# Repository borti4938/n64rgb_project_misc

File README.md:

Miscellaneous PCBs for the N64RGB Project
---

This repository contains several PCBs which I find to be helpful for the N64RGB project.
Here is a small overview.

- [Filter AddOn](./FilterAddOn/): A tiny PCB which adds a video filter to the MultiOut for the analog output
- [Flex PCB N64RGB to MultiOut](./N64RGB2MoutFilter/): A flexible PCB which connects between N64RGBv2.1 or N64Advanced and MultiOut. This flexible is designed to have the filter add on included if wanted.
- [Power Regulator](./PowerReg/): A power regulator connecting to 12V power rail and outputting 3.3V for older N64RGB PCBs (earlier than v2.1) and viletims commercial N64RGB product.
- [Flex PCB RCP-NUS to N64RGB](./RCP2N64RGB/): A flexible PCB which connects between RCP-NUS and N64RGBv2.1 or N64Advanced.
- [Flex PCB RCP-NUS to some wire pads](./RCP2Pads/): A tiny flexible PCB which connects to the RCP-NUS optimized for price. This helps installing a CPLD-/FPGA-based N64RGB PCB with wires to the digital video lines.
- [A simple N64RGB Amp](./simpleRGBamp/): A THS7374 board mostly suitable for a N64 which already outputs RGB (-CPU-01 to -CPU-04 boards).

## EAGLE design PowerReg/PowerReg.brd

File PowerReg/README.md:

Power Regulator for N64RGB DAC
---

### Purpose

This little PCB is designed to used with
- [viletims N64RGB](http://etim.net.au/n64rgb/) project
- older boards from the [N64RGBv1 project](https://github.com/borti4938/n64rgb/tree/master/generalRGBmod/Main-PCB/v1)

This PCB has a regulator on board which generated 3.3V power supply for the mentioned mod-boards. It has been discussed at the [Shmups forums](https://shmups.system11.org/viewtopic.php?f=6&t=61455) that the output suffers from digital noise probably depending on CPU, PPU and APU load.  
Power the replacement RGB DAC from a different power supply source may help to 'decouple' this noise from the analog part.

##### Note
**[1]** Future releases may have a regulator on board. It has not been designed yet.

### Buiding the PCB

You may use any PCB prototype service of your choice or use a pre-existing [OSHPark project](https://oshpark.com/shared_projects/ofIFYk5I).  
**Order the board as thin as possible**; <1.0mm should be fine. This means for OSHPark service use 0.8mm substrate thickness.

### BOM

- U1: one of the following ICs, all SOT223 package (may named differently for each manufacturer)
  - NCP1117ST33T3G
  - TLV1117-33IDCYR
  - SPX1117M3-L-3-3/TR
- C1: 10-100uF/16V+ (SMD0805-1210)
- C2: 10-100uF/6.3V+ (SMD0805-1210)
- C3: 2.2uF / 6.3V+ (SMD0603)

### Installation

0. If not already done: assemble the PCB.
1. If you have an existing installation, first disconnect the 3.3V power supply wire from the modding board.  
   (Please look onto the pin out diagrams if you use viletims board - it may be one wire of the ribbon cable)
2. Solder the PCB under the power switch of the N64 mainboard (upper part) such that the PCB ranges to the inner side.
3. Connect the 3.3V output to the modding PCB

## ENJOY!!!!

### Acknowledgement

Many thanks to Womi ([circuit-board.de](https://circuit-board.de/forum/) user) for testing and giving feedback.  
Also many thanks to the shmups community for the discussion, especially but not limited to leonk, Syntax, kel, viletim, Thomas83lin, and many more...

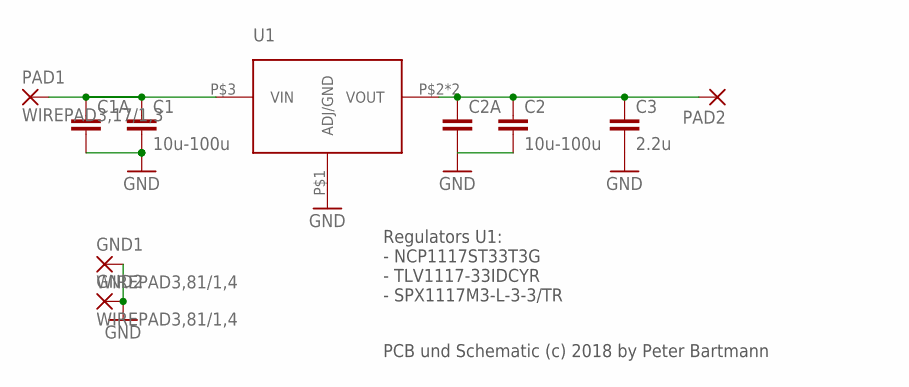
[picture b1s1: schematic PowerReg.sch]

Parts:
C1, C2: 10u-100u; C0805
C1A, C2A: C-EUC1210K; C1210K
C3: 2.2u; C0603
GND1, GND2: WIREPAD3,81/1,4; 3,81/1,4
PAD1: WIREPAD3,17/1,3; 3,17/1,3
PAD2: SMD5; SMD2,54-5,08
U1: SPX1117; SOT-223

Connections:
GND: C1.2, C1A.2, C2.2, C2A.2, C3.2, GND1.1, GND2.1, U1.P$1 (ADJ/GND)
unnamed: C1.1, C1A.1, PAD1.1, U1.P$3 (VIN)
unnamed: C2.1, C2A.1, C3.1, PAD2.1, U1.P$2 (VOUT), U1.P$4 (VOUT)

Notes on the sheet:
Regulators U1: - NCP1117ST33T3G - TLV1117-33IDCYR - SPX1117M3-L-3-3/TR
PCB und Schematic (c) 2018 by Peter Bartmann

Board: 2 copper layers, 10 parts (0 on the bottom side), 3 nets, no tracks yet.

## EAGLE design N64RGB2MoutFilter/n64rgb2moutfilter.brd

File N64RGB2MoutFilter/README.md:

N64RGB2MoutFilter
---

A **flexible** PCB which connects the MultiOut with the [N64 Advanced PCB](https://github.com/borti4938/n64adv_pcb) or [N64RGB PCB](https://github.com/borti4938/n64rgb_pcb).
The connection PCB must be soldered on both ends - one end goes to the MultiOut, the other to the modding board.
To support older PCBs, I decided to go with the solder solution.
I future updates I may replace that and go with a FFC connector on the modding board side.

### Ordering the PCB

You can order the PCB from any manufacturer you like.
OSHPark flex service is fine, also the flex service from PCBWay does a great job.

### Assembly

Order the PCB and source the components as requested by the [BOM sheet](./doc/N64RGB2MoutFilter_BOM.xlsx).
Assembly should be straight forward.
You may print the [assembly sheet](./doc/n64rgb2multiout_assembly_sheet_top.pdf) for your orientation.

Please note that you have the option to include the [Filter AddOn](../FilterAddOn) on the flexible PCB or just leave it.
I recommend using the filter.

If you use a PCBA service, you may use the provided mounting file ([with filter](./doc/n64rgb2moutfilter_filteroption.mnt) or [without filter](./doc/n64rgb2moutfilter_nofilter.mnt)).

### Installation

Please read the installation guide of the [N64 Advanced PCB](https://github.com/borti4938/n64adv_pcb) or [N64RGB PCB](https://github.com/borti4938/n64rgb_pcb).

### Jumper Description

Use of SJ1 and SJ3 is also described in the installation guide of the [N64 Advanced PCB](https://github.com/borti4938/n64adv_pcb) or [N64RGB PCB](https://github.com/borti4938/n64rgb_pcb).
Just follow this guide and you came across to the point where you work with them.

#### SJ1

Jumper matrix determine sync source at MultiOut
 - Jumper at 1a forwarding TTL sync
 - Jumper at 1b forwarding 75ohm sync
 - number next to each particular jumper determines the pin of the MultiOut where the signal is forwarded to
 - You are not allowed to short two times the same number!
 
Examples:
 - Closing _1a - 3_ forwards TTL sync to pin 3 of the MultiOut
 - Closing _1b - 7_ forwards 75ohm sync to pin 7 of the MultiOut
 - It is not allowed to close _1a - 3_ and _1b - 3_ at the same time
 - It is allowed to close _1b - 3_, _1b - 7_ and _1b - 9_ at the same time

#### SJ2

flex assembly setup (see [BOM sheet](./doc/N64RGB2MoutFilter_BOM.xlsx))
 - close all three jumpers if you do not use the filter assembly

#### SJ3

Sync source at the modding board
 - J3.1: Use TTL C-Sync (true TTL setup)
 - J3.2: Use 75ohm Sync (75ohm setup)
 - Never use both!

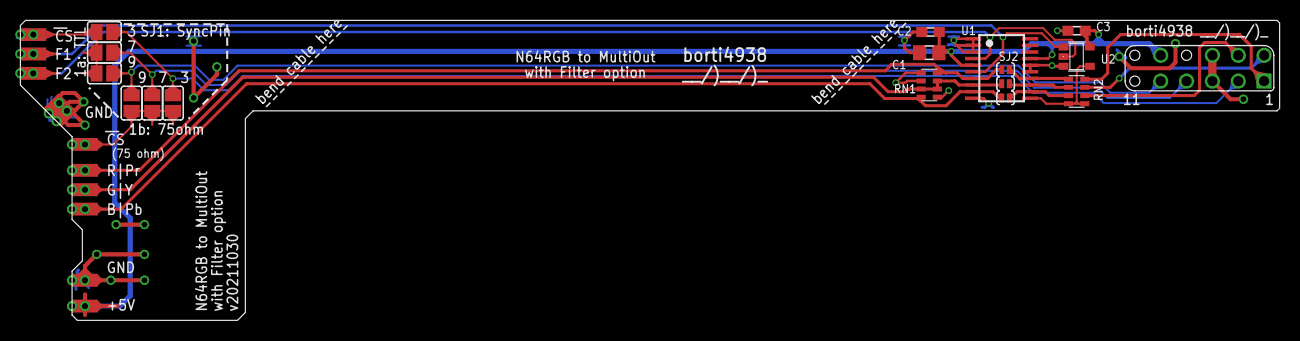
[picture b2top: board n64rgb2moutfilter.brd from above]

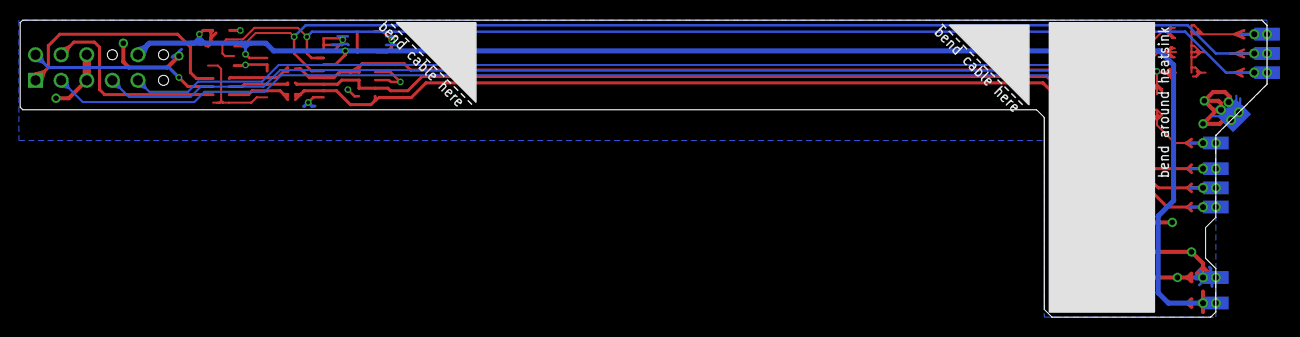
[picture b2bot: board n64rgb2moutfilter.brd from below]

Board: 2 copper layers, 123.7 x 29.5 mm, 39 parts (11 on the bottom side), 19 nets.

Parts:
B/PB, B/PB1: SMD1,27-2,54
C1: 22u; C0805
C2, C3: 0.1u; C0603
CS75#, CS75#1: SMD1,27-2,54
CS#, CS#1: SMD1,27-2,54
E$1: SNES_MULTIAV_RGBSYFBAS
E$2, E$3, E$4, E$5, E$6, E$7: SJ
F1, F2, F3, F4: SMD1,27-2,54
G/Y, G/Y1: SMD1,27-2,54
P_GND1, P_GND2, P_GND3, P_GND4, P_GND5, P_GND6: SMD1,27-2,54
P_VCC_5V, P_VCC_5V1: SMD1,27-2,54
R/PR, R/PR1: SMD1,27-2,54
RN1, RN2: 75; CTS742C083
SJ2B, SJ2G, SJ2R: SJ_SMALL
U1: THS7368
U2: SOT23-5

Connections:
5V: C1.2, C2.1, C3.1, E$1.10, P_VCC_5V.1, P_VCC_5V1.1, U1.5, U1.17, U2.5
#CS: E$1.3, E$2.2, E$7.2
#CS.75.I: CS75#.1, CS75#1.1, E$5.1, E$6.1, E$7.1
#CS.I: CS#.1, CS#1.1, E$2.1, E$3.1, E$4.1
BLUE: B/PB.1, B/PB1.1, RN1.8, SJ2R.1, U1.9
BLUE.OUT: RN2.3, SJ2R.2, U1.12
BLUE.OUT.75: E$1.4, RN2.6
BYPASS_SF: RN2.4, RN2.5, U1.11, U2.4
F1: F1.1, F4.1, U1.6, U2.1
F2: F2.1, F3.1, U1.4, U2.2
FBAS: E$1.9, E$4.2, E$5.2
GND: C1.1, C2.2, C3.2, E$1.5, E$1.6, P_GND1.1, P_GND2.1, P_GND3.1, P_GND4.1, P_GND5.1, P_GND6.1, RN1.1, RN1.5, RN1.6, U1.1, U1.2, U1.3, U1.10, U1.15, U1.16, U2.3
GREEN: G/Y.1, G/Y1.1, RN1.2, RN1.3, RN1.7, SJ2G.1, U1.8
GREEN.OUT: RN2.2, SJ2G.2, U1.13
GREEN.OUT.75: E$1.2, RN2.7
LUMA: E$1.7, E$3.2, E$6.2
RED: R/PR.1, R/PR1.1, RN1.4, SJ2B.1, U1.7
RED1.OUT: RN2.1, SJ2B.2, U1.14
RED.OUT.75: E$1.1, RN2.8

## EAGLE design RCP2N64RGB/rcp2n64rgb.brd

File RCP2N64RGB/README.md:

RCP2N64RGB
---

A **flexible** PCB which connects the RCP-NUS (graphical processor of the N64) with the [N64 Advanced PCB](https://github.com/borti4938/n64adv_pcb) or [N64RGB PCB](https://github.com/borti4938/n64rgb_pcb).
The connection PCB must be soldered on both ends - one end goes to the RCP-NUS, the other to the modding board.
To support older PCBs, I decided to go with the solder solution.
I future updates I may replace that and go with a FFC connector on the modding board side.

### Ordering the PCB

You can order the PCB from any manufacturer you like.
OSHPark flex service is fine, also the flex service from PCBWay does a great job.

### Assembly

Order the PCB and source the components as requested by the [BOM sheet](./doc/RCP2N64RGB_BOM.xlsx).
Assembly should be straight forward.
The ferrite bead / resistor arrays don't have an orientation.

You may print the [assembly sheet](./doc/rcp2n64rgb_assembly_sheet_top.pdf) for your orientation.
If you use a PCBA service, you may use the provided [mounting file](./doc/rcp2n64rgb.mnt).

### Installation

Please read the installation guide of the [N64 Advanced PCB](https://github.com/borti4938/n64adv_pcb) or [N64RGB PCB](https://github.com/borti4938/n64rgb_pcb).

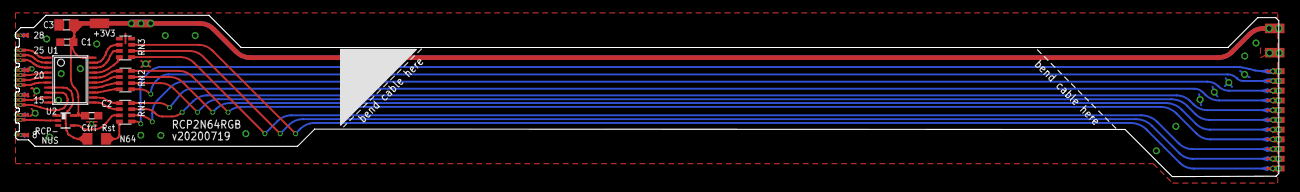
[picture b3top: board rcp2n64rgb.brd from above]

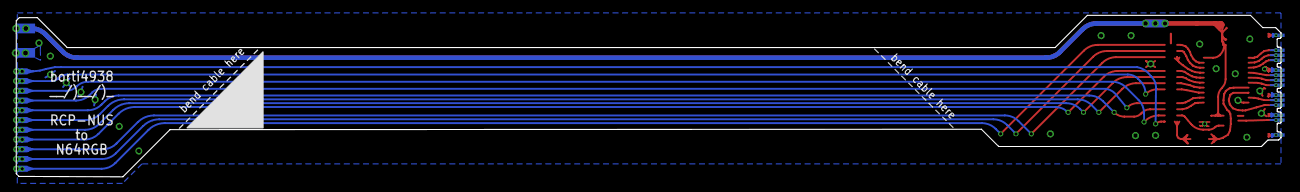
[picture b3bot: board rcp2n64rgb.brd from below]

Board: 2 copper layers, 164.9 x 21.1 mm, 65 parts (27 on the bottom side), 34 nets.

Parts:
/RST_A, /RST_A1: SMD0,8-1,6
C1, C2: 0.1u; C0603
C3: 22u; C0805
CLOCK#, CLOCK#1: SMD0,8-1,6
CTRL_A, CTRL_A1: SMD0,8-1,6
D0, D1, D2, D3, D4, D5, D6, D7, D8, D9, D10, D11, D12, D13: SMD0,8-1,6
DSYNC#, DSYNC#1: SMD0,8-1,6
E$2, E$6: SMD0.8SQ
E$8, E$9, E$10, E$11, E$12, E$13, E$14, E$15, E$16, E$17, E$18, E$19, E$22, E$23, E$24, E$25, E$26, E$27, E$28, E$29, E$30, E$31, E$32, E$33, E$43, E$46, E$47: SMD0,45-1,35
GND: SMD0,45-1,35
P_GND0, P_GND1: SMD1,27-2,54
P_VCC_3V, P_VCC_3V1, P_VCC_3V3: SMD1,27-2,54
RN1, RN2, RN3: CTS742C083
U1: 74VHC9151FT; TSSOP20
U2: SN74LVC1G17DCKR; DCK_R-PDSO-G5

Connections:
3V3: C1.1, C2.1, C3.1, P_VCC_3V.1, P_VCC_3V1.1, P_VCC_3V3.1, U1.20, U2.5
#DSYNC: E$10.P$1, E$31.P$1, U1.8
#DSYNC.1: DSYNC#.P$1, DSYNC#1.P$1, RN1.8
CTRL: E$2.P$1, U1.7
CTRL.1: CTRL_A.P$1, CTRL_A1.P$1, RN2.5
D0: E$19.P$1, E$22.P$1, U1.1
D0.1: D0.P$1, D7.P$1, RN3.7
D1: E$18.P$1, E$23.P$1, U1.2
D1.1: D1.P$1, D8.P$1, RN3.6
D2: E$17.P$1, E$24.P$1, U1.3
D2.1: D2.P$1, D9.P$1, RN3.5
D3: E$15.P$1, E$26.P$1, U1.4
D3.1: D3.P$1, D10.P$1, RN2.8
D4: E$14.P$1, E$27.P$1, U1.5
D4.1: D4.P$1, D11.P$1, RN2.7
D5: E$13.P$1, E$28.P$1, U1.6
D5.1: D5.P$1, D12.P$1, RN2.6
D6: E$11.P$1, E$30.P$1, U1.9
D6.1: D6.P$1, D13.P$1, RN1.7
GND: C1.2, C2.2, C3.2, E$9.P$1, E$12.P$1, E$16.P$1, E$25.P$1, E$29.P$1, E$32.P$1, E$43.P$1, E$46.P$1, GND.P$1, P_GND0.1, P_GND1.1, RN3.1, RN3.8, U1.10, U2.3
RST: E$6.P$1, RN1.4
RST.1: /RST_A.P$1, /RST_A1.P$1, RN1.5
S$1: RN3.2, U1.19
S$2: RN3.3, U1.18
S$3: RN3.4, U1.17
S$4: RN2.1, U1.16
S$6: RN2.2, U1.15
S$7: RN2.3, U1.14
S$9: RN1.1, U1.12
S$10: RN2.4, U1.13
S$11: RN1.3, U2.4
S$12: RN1.2, U1.11
VCLK: E$8.P$1, E$33.P$1, U2.2
VCLK.1: CLOCK#.P$1, CLOCK#1.P$1, RN1.6

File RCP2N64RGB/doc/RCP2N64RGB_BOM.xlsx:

No. of PCBs | 3
Designator | MPN | QTY per PCB | QTY | DESCRIPTION | VALUE | PACKAGE | NOTES
U1 | 74VHC9151FT | 1 | 3 | 9bit Buffer, Schmitt-Triggered, non-inverting |  | TSSOP20
U2 | SN74LVC1G17DCKR | 1 | 3 | Buffer, Schmitt-Triggered, non-inverting |  | SO70-5
C1,C2 |  | 1 | 3 | Ceramic capacitor, X8L | 0.1uF / 50V | SMD0603
C3 |  | 1 | 3 | Ceramic capacitor, X5R | 22uF / 6.3V | SMD0805
RN1,RN2,RN3 | BK32164M121-T | 3 | 9 | Resistor Array (4x) | 4x ferrit bead | SMD1206 | Either this, …
 | CAT16-000J4LF / CAY16-000J4LF |  |  | Resistor Array (4x) | 4x 0ohm | SMD1206 | … or that for RN1-RN3

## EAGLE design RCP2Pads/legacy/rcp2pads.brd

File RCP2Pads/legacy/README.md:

# A small Flex-PCB
## N64 RCP-NUS breakout

## Purpose

This PCB enables you to apply conditioning resistors to the RCP output pins. This is useful for any CPLD and FPGA RGB Kit like viletims N64RGB (public and commercial), N64RGBv1, N64RGBv2, N64Advanced and many more variations spread over the internet.

## Pinout

From top to bottom (RCP on left, connector right)

| **Pin** | **Signal** |
|:-------:|:-----------|
| 17 | GND |
| 16 | D0 |
| 15 | D1 |
| 14 | D2 |
| 13 | D3 |
| 12 | D4 |
| 11 | D5 |
| 10 | D6 |
| 9 | #DSYNC |
| 8 | VCLK |
| 7 | GND |
| 6 | LRCLK (Audio, A2) |
| 5 | SDATA (Audio, A1) |
| 4 | SCLK (Audio, A0) |
| 3 | GND |
| 2 | Ctrl. (controller port pin 2, pin 16 PIF-NUS) |
| 1 | Rst (pin 27 PIF-NUS) |

## Preparation

You need

- four resistor arrays: 4x47ohm parallel, SMD1206, e.g. CAT16-47R0F4LF / CAY16-47R0F4LF
- if you have resistors at the input of your N64RGB modding board, you need to replace them with ferrite beads (see BOM if for proper replacements)

Assemble the board. The resistor arrays don't have an orientation.

## Installation

Solder the FPC board to the output pins 6 - 28 (pin 5 has a dot, pin 30 also) of the RCP-NUS.

Connect pad for Ctrl. and Rst. as stated in the table above. More information about appropriate solder points can be found in the Guide.

Use the pads to connect your modding kit. Note the pinout of the modding kit. If possible, keep/run VCLK separated from data wires.

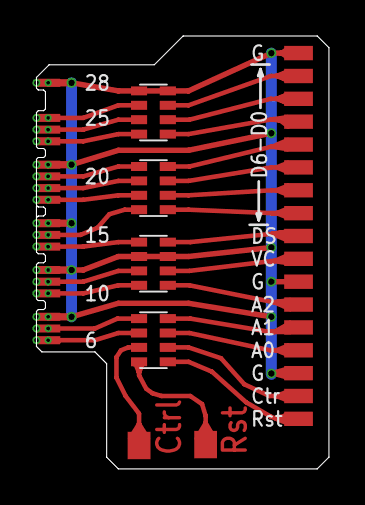
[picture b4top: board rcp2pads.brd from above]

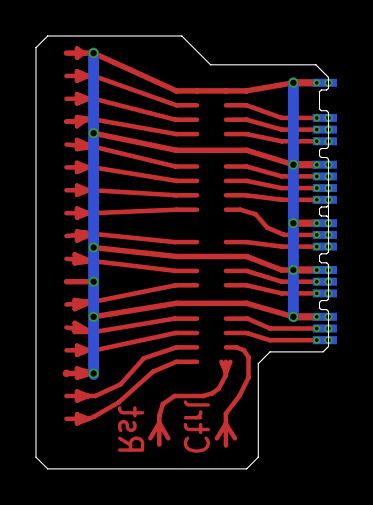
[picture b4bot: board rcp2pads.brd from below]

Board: 2 copper layers, 16.2 x 24.1 mm, 57 parts (17 on the bottom side), 29 nets.

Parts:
E$1, E$3, E$4, E$5: CTS742C083
E$2, E$6: SMD0.8SQ
E$8, E$9, E$10, E$11, E$12, E$13, E$14, E$15, E$16, E$17, E$18, E$19, E$22, E$23, E$24, E$25, E$26, E$27, E$28, E$29, E$30, E$31, E$32, E$33, E$38, E$40, E$41, E$42, E$43, E$44, E$45, E$46, E$47: SMD0,45-1,35
E$20, E$21, E$36, E$39, E$48, E$49, E$50, E$51, E$53, E$54, E$55, E$56, E$57, E$58, E$59, E$60, E$61: SMD0,8-1,6
GND: SMD0,45-1,35

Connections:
#DSYNC: E$5.1, E$10.P$1, E$31.P$1
#DSYNC.1: E$5.8, E$53.P$1
CTRL: E$1.7, E$2.P$1
CTRL.1: E$1.2, E$60.P$1
D0: E$3.2, E$19.P$1, E$22.P$1
D0.1: E$3.7, E$20.P$1
D1: E$3.3, E$18.P$1, E$23.P$1
D1.1: E$3.6, E$36.P$1
D2: E$3.4, E$17.P$1, E$24.P$1
D2.1: E$3.5, E$39.P$1
D3: E$4.1, E$15.P$1, E$26.P$1
D3.1: E$4.8, E$48.P$1
D4: E$4.2, E$14.P$1, E$27.P$1
D4.1: E$4.7, E$49.P$1
D5: E$4.3, E$13.P$1, E$28.P$1
D5.1: E$4.6, E$50.P$1
D6: E$4.4, E$11.P$1, E$30.P$1
D6.1: E$4.5, E$51.P$1
GND: E$3.1, E$3.8, E$5.2, E$5.7, E$9.P$1, E$12.P$1, E$16.P$1, E$21.P$1, E$25.P$1, E$29.P$1, E$32.P$1, E$43.P$1, E$46.P$1, E$55.P$1, E$59.P$1, GND.P$1
LRCLK: E$5.4, E$38.P$1
LRCLK.1: E$5.5, E$56.P$1
RST: E$1.8, E$6.P$1
RST.1: E$1.1, E$61.P$1
SCLK: E$1.6, E$41.P$1
SCLK.1: E$1.3, E$58.P$1
SDATA: E$1.5, E$40.P$1
SDATA.1: E$1.4, E$57.P$1
VCLK: E$5.3, E$8.P$1, E$33.P$1
VCLK.1: E$5.6, E$54.P$1

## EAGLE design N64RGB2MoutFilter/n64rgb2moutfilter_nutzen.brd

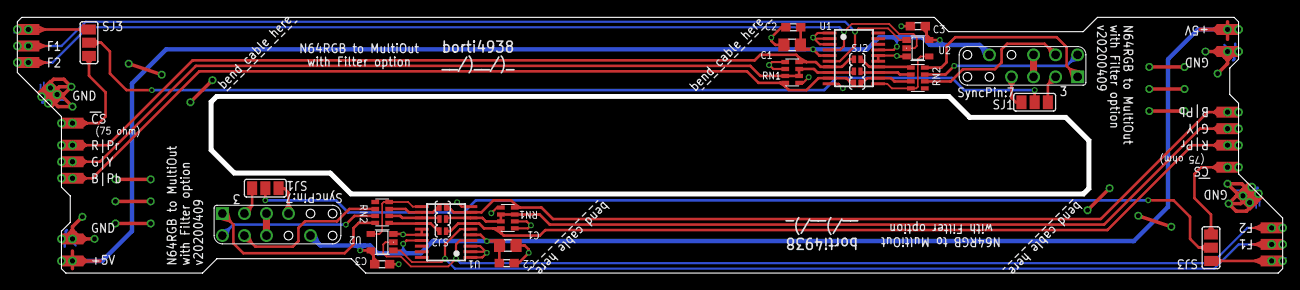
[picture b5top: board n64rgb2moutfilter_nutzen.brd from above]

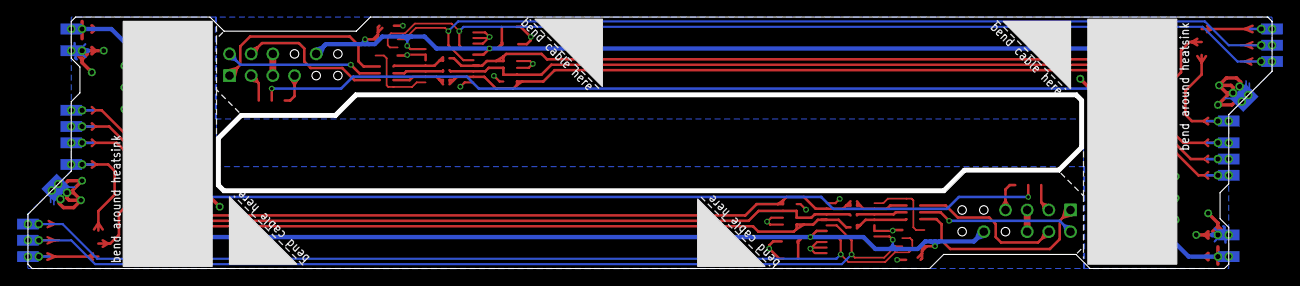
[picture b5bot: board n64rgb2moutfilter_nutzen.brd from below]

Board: 2 copper layers, 145.8 x 29.5 mm, 70 parts (22 on the bottom side), 38 nets.

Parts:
B/PB, B/PB1, B/PB2, B/PB3: SMD1,27-2,54
C1, C4: 22u; C0805
C2, C3, C5, C6: 0.1u; C0603
CS75#, CS75#1, CS75#2, CS75#3: SMD1,27-2,54
CS#, CS#1, CS#2, CS#3: SMD1,27-2,54
E$1, E$2: SNES_MULTIAV_RGBSY
F1, F2, F3, F4, F5, F6, F7, F8: SMD1,27-2,54
G/Y, G/Y1, G/Y2, G/Y3: SMD1,27-2,54
P_GND1, P_GND2, P_GND3, P_GND4, P_GND5, P_GND6, P_GND7, P_GND8, P_GND9, P_GND10, P_GND11, P_GND12: SMD1,27-2,54
P_VCC_5V, P_VCC_5V1, P_VCC_5V2, P_VCC_5V3: SMD1,27-2,54
R/PR, R/PR1, R/PR2, R/PR3: SMD1,27-2,54
RN1, RN2, RN3, RN4: 75; CTS742C083
SJ1, SJ2, SJ3, SJ4: SJ_2
SJ2B, SJ2B1, SJ2G, SJ2G1, SJ2R, SJ2R1: SJ_SMALL
U1, U3: THS7368
U2, U4: SOT23-5

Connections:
5V: C1.2, C2.1, C3.1, E$1.10, P_VCC_5V.1, P_VCC_5V1.1, U1.5, U1.17, U2.5
5V1: C4.2, C5.1, C6.1, E$2.10, P_VCC_5V2.1, P_VCC_5V3.1, U3.5, U3.17, U4.5
#CS: E$1.3, SJ1.1
#CS1: E$2.3, SJ2.1
#CS.75.I: CS75#.1, CS75#1.1, SJ3.3
#CS.75.I1: CS75#2.1, CS75#3.1, SJ4.3
#CS.I: CS#.1, CS#1.1, SJ3.1
#CS.I1: CS#2.1, CS#3.1, SJ4.1
#CS.SEL: SJ1.2, SJ3.2
#CS.SEL1: SJ2.2, SJ4.2
BLUE: B/PB.1, B/PB1.1, RN1.8, SJ2R.1, U1.9
BLUE1: B/PB2.1, B/PB3.1, RN3.8, SJ2R1.1, U3.9
BLUE.OUT: RN2.3, SJ2R.2, U1.12
BLUE.OUT1: RN4.3, SJ2R1.2, U3.12
BLUE.OUT.1: E$2.4, RN4.6
BLUE.OUT.75: E$1.4, RN2.6
BYPASS_SF: RN2.4, U1.11, U2.4
BYPASS_SF1: RN4.4, U3.11, U4.4
F1: F1.1, F4.1, U1.6, U2.1
F2: F2.1, F3.1, U1.4, U2.2
F3: F5.1, F8.1, U3.6, U4.1
F4: F6.1, F7.1, U3.4, U4.2
GND: C1.1, C2.2, C3.2, E$1.5, E$1.6, P_GND1.1, P_GND2.1, P_GND3.1, P_GND4.1, P_GND5.1, P_GND6.1, RN1.1, RN1.5, RN1.6, U1.1, U1.2, U1.3, U1.10, U1.15, U1.16, U2.3
GND1: C4.1, C5.2, C6.2, E$2.5, E$2.6, P_GND7.1, P_GND8.1, P_GND9.1, P_GND10.1, P_GND11.1, P_GND12.1, RN3.1, RN3.5, RN3.6, U3.1, U3.2, U3.3, U3.10, U3.15, U3.16, U4.3
GREEN: G/Y.1, G/Y1.1, RN1.2, RN1.3, RN1.7, SJ2G.1, U1.8
GREEN1: G/Y2.1, G/Y3.1, RN3.2, RN3.3, RN3.7, SJ2G1.1, U3.8
GREEN.OUT: RN2.2, SJ2G.2, U1.13
GREEN.OUT1: RN4.2, SJ2G1.2, U3.13
GREEN.OUT.1: E$2.2, RN4.7
GREEN.OUT.75: E$1.2, RN2.7
LUMA: E$1.7, SJ1.3
LUMA1: E$2.7, SJ2.3
RED: R/PR.1, R/PR1.1, RN1.4, SJ2B.1, U1.7
RED1: R/PR2.1, R/PR3.1, RN3.4, SJ2B1.1, U3.7
RED1.OUT: RN2.1, SJ2B.2, U1.14
RED1.OUT1: RN4.1, SJ2B1.2, U3.14
RED.OUT.1: E$2.1, RN4.8
RED.OUT.75: E$1.1, RN2.8

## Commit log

2022-03-26 add submodule
2022-03-26 add license and readme
2022-03-27 add legacy RCP2Pads design
2022-03-30 move pcb gerber to subfolder
2022-07-13 increase flex by 1.5cm for easier routing
2022-07-13 update flex n64rgb2moutfilter to v20211030: - add sync jumper matrix - remove panel file and gerber

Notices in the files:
N64RGB2MoutFilter/n64rgb2moutfilter.brd:
Flex-PCB (c) 2019 - 2021 Peter Bartmann
N64RGB2MoutFilter/n64rgb2moutfilter_nutzen.brd:
Flex-PCB (c) 2019, 2020 Peter Bartmann
